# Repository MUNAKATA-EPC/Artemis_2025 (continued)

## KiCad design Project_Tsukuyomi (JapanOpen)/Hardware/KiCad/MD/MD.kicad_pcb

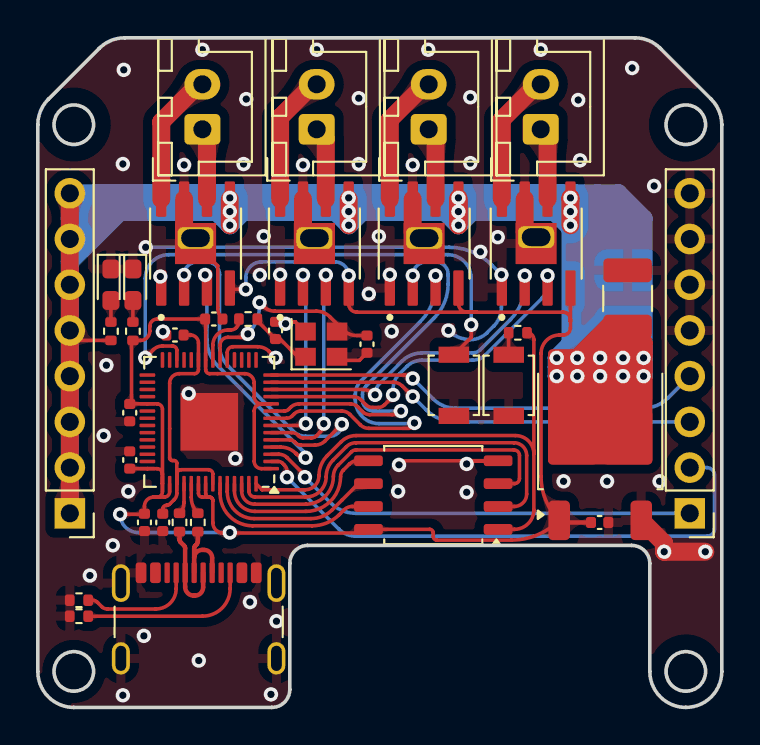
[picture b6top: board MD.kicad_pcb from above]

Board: 2 copper layers, 38.0 x 37.2 mm, 37 parts (0 on the bottom side), 43 nets.

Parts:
C1, C2: C_Small; C_0402_1005Metric
C3, C4, C5, C6, C7, C9, C11: 0.1μ; C_0402_1005Metric
C10: 0.1μ; C_1210_3225Metric_Pad1.33x2.70mm_HandSolder
D2, D3: LED; LED_0603_1608Metric_Pad1.05x0.95mm_HandSolder
J1: USB_C_Receptacle_USB2.0; USB_C_Receptacle_GCT_USB4105-xx-A_16P_TopMnt_Horizontal
J2, J3: Conn_01x08_Socket; PinHeader_1x08_P2.54mm_Vertical
J4, J5, J6, J7: Conn_01x02_Socket; JST_XH_B2B-XH-A_1x02_P2.50mm_Vertical
R1, R2: 5.1k; R_0402_1005Metric
R3, R4: 27; R_0402_1005Metric
R5, R6, R8: 1k; R_0402_1005Metric
R9: 100; R_0402_1005Metric
SW1, SW2: SW_Push; SW_SPST_B3U-1000P
U1: W25Q128JVS; SOIC-8_5.23x5.23mm_P1.27mm
U2: RP2040; QFN-56-1EP_7x7mm_P0.4mm_EP3.2x3.2mm
U3, U4, U5, U6: TB67H450FNG_EL; SOIC127P599X175-9N
U7: AZ1084-3.3; TO-252-2
Y1: Crystal_GND24; Crystal_SMD_2520-4Pin_2.5x2.0mm

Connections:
+1V1: C3.2, C4.2, U2.23 (DVDD), U2.45 (VREG_VOUT), U2.50 (DVDD)
+3.3V: C5.2, C6.2, C7.2, C9.2, C11.2, R9.1, U1.8 (VCC), U2.1 (IOVDD), U2.10 (IOVDD), U2.22 (IOVDD), U2.33 (IOVDD), U2.42 (IOVDD), U2.43 (ADC_AVDD), U2.44 (VREG_IN), U2.48 (USB_VDD), U2.49 (IOVDD), U3.4 (VREF), U4.4 (VREF), U5.4 (VREF), U6.4 (VREF), U7.2 (VO)
+12V: C10.2, J2.1, J2.2, J2.3, J2.4, J2.5, J2.6, J2.7, J2.8, R8.1, U3.5 (VM), U4.5 (VM), U5.5 (VM), U6.5 (VM), U7.3 (VO)
/BLDC1: J3.3, U2.13 (GPIO10)
/BLDC2: J3.4, U2.14 (GPIO11)
/BOOT: R5.1, SW2.1
/D+: R4.2, U2.47 (USB_DP)
/D-: R3.2, U2.46 (USB_DM)
/IN1A: U2.4 (GPIO2), U3.3 (IN1)
/IN1B: U2.5 (GPIO3), U3.2 (IN2)
/IN2A: U2.6 (GPIO4), U5.3 (IN1)
/IN2B: U2.7 (GPIO5), U5.2 (IN2)
/IN3A: U2.8 (GPIO6), U4.3 (IN1)
/IN3B: U2.9 (GPIO7), U4.2 (IN2)
/IN4A: U2.11 (GPIO8), U6.3 (IN1)
/IN4B: U2.12 (GPIO9), U6.2 (IN2)
/MDRX: J3.2, U2.2 (GPIO0)
/MDTX: J3.1, U2.3 (GPIO1)
/Motor1A: J4.1, U3.6 (OUT1)
/Motor1B: J4.2, U3.8 (OUT2)
/Motor2A: J5.1, U5.6 (OUT1)
/Motor2B: J5.2, U5.8 (OUT2)
/Motor3A: J6.1, U4.6 (OUT1)
/Motor3B: J6.2, U4.8 (OUT2)
/Motor4A: J7.1, U6.6 (OUT1)
/Motor4B: J7.2, U6.8 (OUT2)
/RUN: SW1.1, U2.26 (RUN)
GND: C1.2, C2.1, C3.1, C4.1, C5.1, C6.1, C7.1, C9.1, C10.1, C11.1, D2.1 (K), D3.1 (K), J1.A1 (GND), J1.A12 (GND), J1.B1 (GND), J1.B12 (GND), J1.S1 (SHIELD), J3.5, J3.6, J3.7, J3.8, R1.2, R2.2, SW1.2, SW2.2, U1.4 (GND), U2.19 (TESTEN), U2.57 (GND), U3.1 (GND), U3.7 (RS), U3.9 (GND), U4.1 (GND), U4.7 (RS), U4.9 (GND), U5.1 (GND), U5.7 (RS), U5.9 (GND), U6.1 (GND), U6.7 (RS), U6.9 (GND), U7.1 (GND), Y1.2, Y1.4
unnamed: C2.2, R6.2, Y1.1
unnamed: D2.2 (A), R8.2
unnamed: D3.2 (A), R9.2
unnamed: J1.A5 (CC1), R1.1
unnamed: J1.B5 (CC2), R2.1
unnamed: J1.A6 (D+), J1.B6 (D+), R4.1
unnamed: J1.A7 (D-), J1.B7 (D-), R3.1
unnamed: U1.6 (CLK), U2.52 (QSPI_SCLK)
unnamed: U1.5 (DI(IO0)), U2.53 (QSPI_SD0)
unnamed: U1.2 (DO(IO1)), U2.55 (QSPI_SD1)
unnamed: U1.3 (IO2), U2.54 (QSPI_SD2)
unnamed: U1.7 (IO3), U2.51 (QSPI_SD3)
unnamed: R5.2, U1.1 (~CS), U2.56 (QSPI_SS)
unnamed: C1.1, U2.20 (XIN), Y1.3
unnamed: R6.1, U2.21 (XOUT)

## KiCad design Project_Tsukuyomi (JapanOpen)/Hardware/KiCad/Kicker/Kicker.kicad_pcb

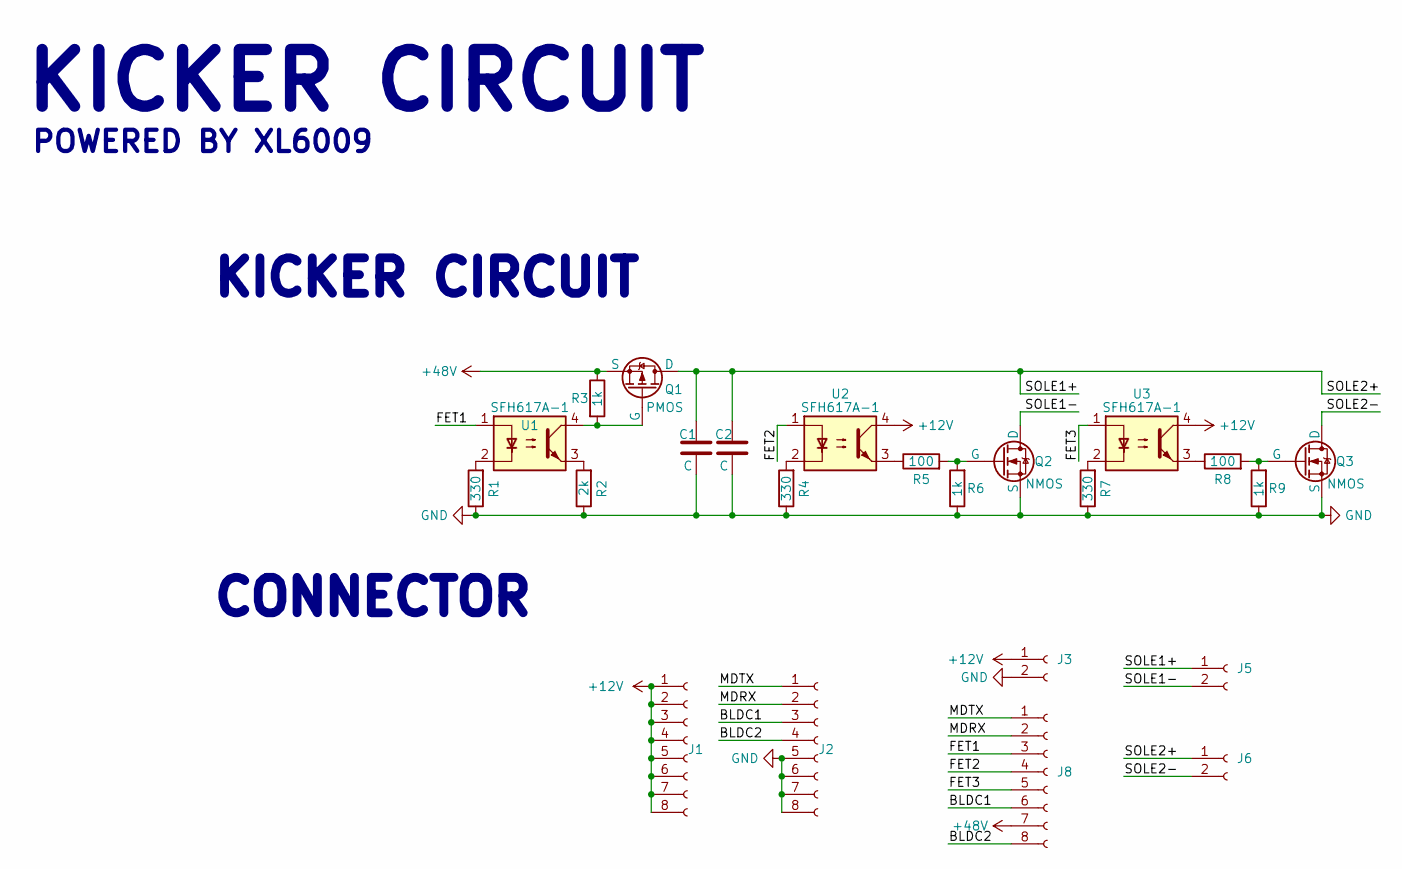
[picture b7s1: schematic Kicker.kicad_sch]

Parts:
C1, C2: C; JST_XH_B2B-XH-A_1x02_P2.50mm_Vertical
J1, J2: Conn_01x08_Socket; PinSocket_1x08_P2.54mm_Vertical
J3: Conn_01x02_Socket; AMASS_XT30PW-F_1x02_P2.50mm_Horizontal
J5, J6: Conn_01x02_Socket; JST_XH_B2B-XH-A_1x02_P2.50mm_Vertical
J8: Conn_01x08_Socket; PinHeader_2x06_P2.54mm_Horizontal
Q1: PMOS; TO-252-2
Q2, Q3: NMOS; LFPAK56
R1, R4, R7: 330; R_Axial_DIN0204_L3.6mm_D1.6mm_P5.08mm_Horizontal
R2: 2k; R_Axial_DIN0204_L3.6mm_D1.6mm_P5.08mm_Horizontal
R3, R6, R9: 1k; R_Axial_DIN0204_L3.6mm_D1.6mm_P5.08mm_Horizontal
R5, R8: 100; R_Axial_DIN0204_L3.6mm_D1.6mm_P5.08mm_Horizontal
U1, U2, U3: SFH617A-1; DIP-4_W7.62mm

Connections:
+12V: J1.1, J1.2, J1.3, J1.4, J1.5, J1.6, J1.7, J1.8, J3.1, U2.4, U3.4
+48V: Q1.3 (S), R3.1; also elsewhere on the board
/BLDC1: J2.3; also elsewhere on the board
/BLDC2: J2.4; also elsewhere on the board
/FET1: U1.1; also elsewhere on the board
/FET2: U2.1; also elsewhere on the board
/FET3: U3.1; also elsewhere on the board
/MDRX: J2.2; also elsewhere on the board
/MDTX: J2.1; also elsewhere on the board
/SOLE1+: C1.1, C2.1, J5.1, J6.1, Q1.1 (D)
/SOLE1-: J5.2, Q2.1 (D)
/SOLE2-: J6.2, Q3.1 (D)
GND: C1.2, C2.2, J2.5, J2.6, J2.7, J2.8, J3.2, Q2.3 (S), Q3.3 (S), R1.1, R2.1, R4.1, R6.1, R7.1, R9.1
unnamed: Q1.2 (G), R3.2, U1.4
unnamed: Q2.2 (G), R5.2, R6.2
unnamed: Q3.2 (G), R8.2, R9.2
unnamed: R1.2, U1.2
unnamed: R2.2, U1.3
unnamed: R4.2, U2.2
unnamed: R5.1, U2.3
unnamed: R7.2, U3.2
unnamed: R8.1, U3.3

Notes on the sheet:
KICKER CIRCUIT
POWERED BY XL6009
CONNECTOR

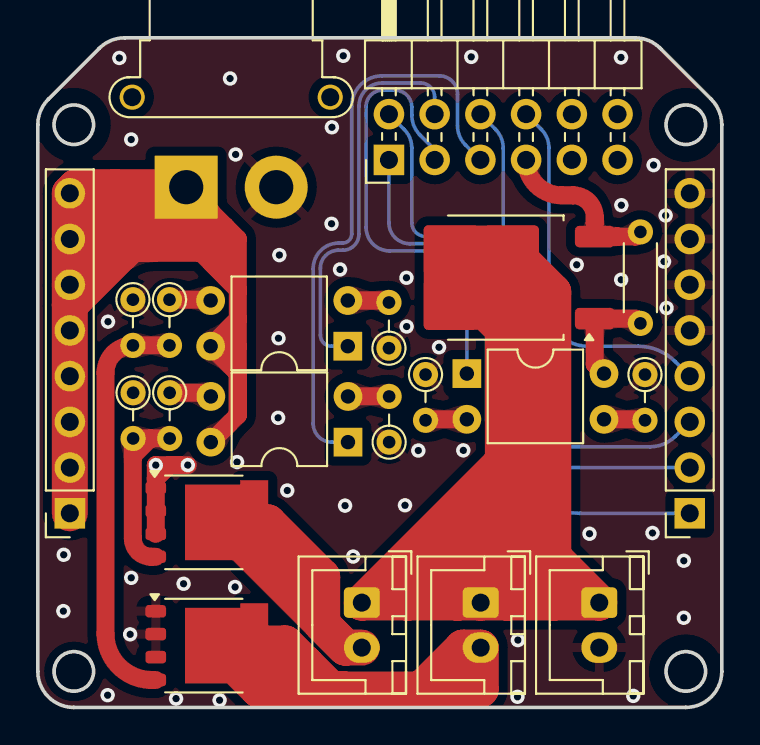
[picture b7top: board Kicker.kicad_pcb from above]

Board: 2 copper layers, 38.0 x 37.2 mm, 22 parts (0 on the bottom side), 22 nets.

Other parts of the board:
J4: Conn_01x08_Socket; PinHeader_2x06_P2.54mm_Horizontal

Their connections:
+48V: J4.7; also elsewhere on the board
/BLDC1: J4.6; also elsewhere on the board
/BLDC2: J4.8; also elsewhere on the board
/FET1: J4.3; also elsewhere on the board
/FET2: J4.4; also elsewhere on the board
/FET3: J4.5; also elsewhere on the board
/MDRX: J4.2; also elsewhere on the board
/MDTX: J4.1; also elsewhere on the board

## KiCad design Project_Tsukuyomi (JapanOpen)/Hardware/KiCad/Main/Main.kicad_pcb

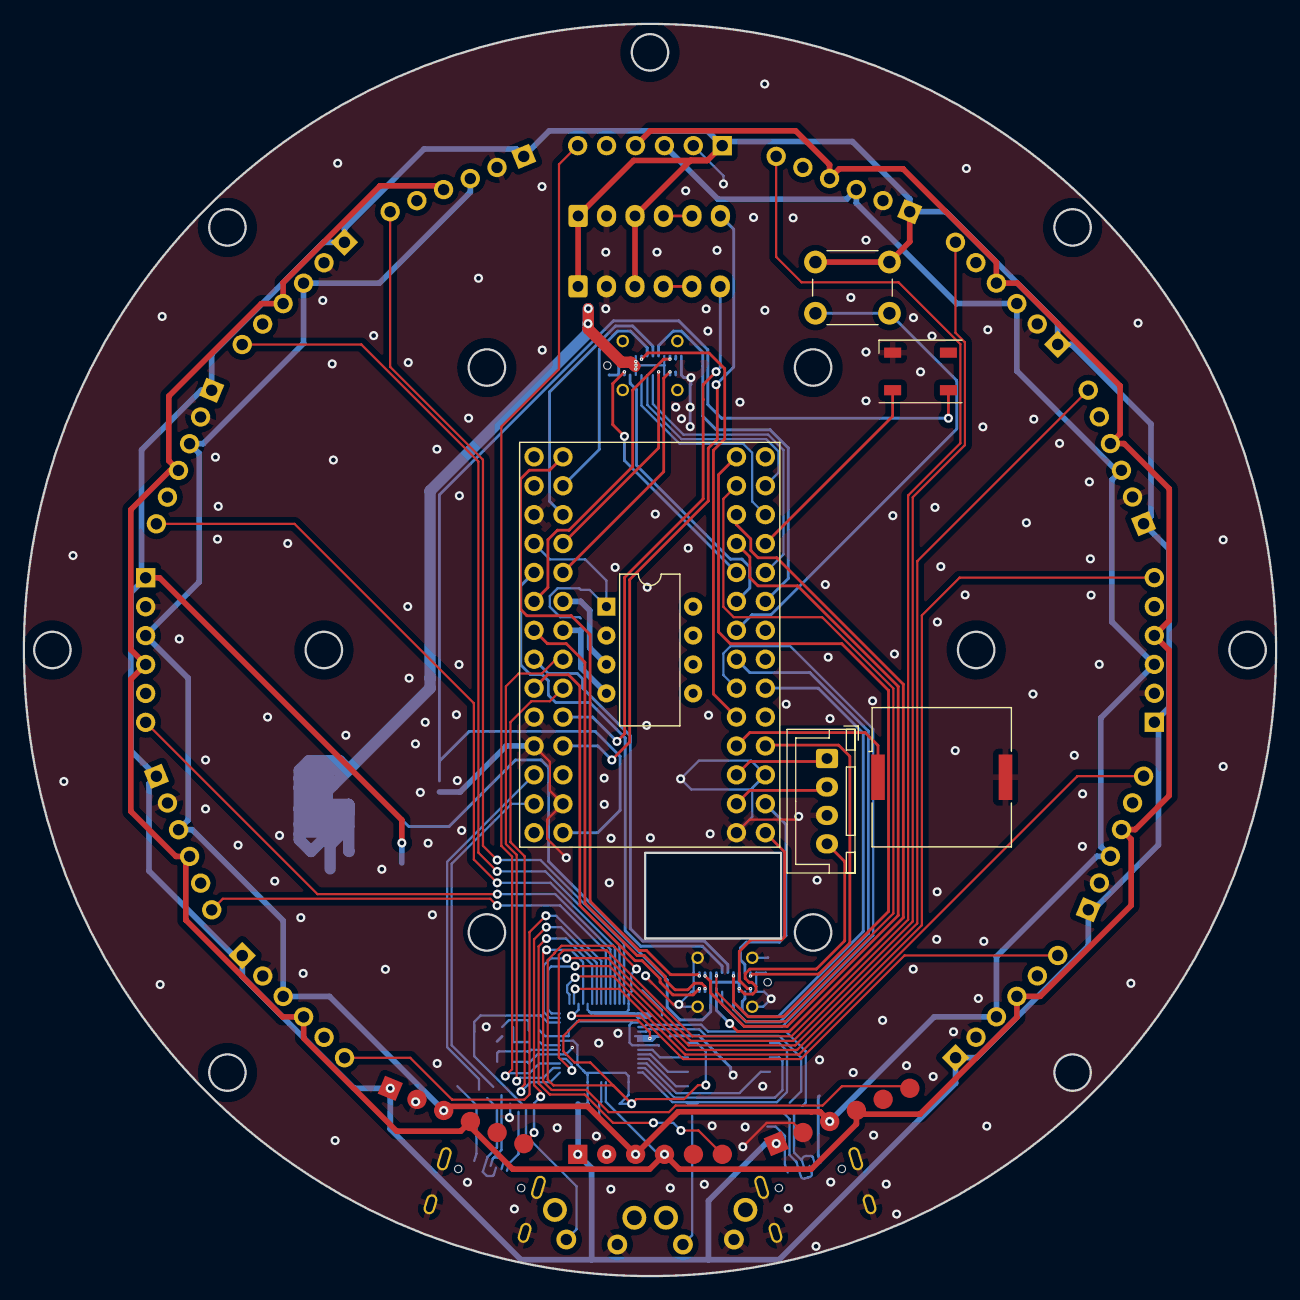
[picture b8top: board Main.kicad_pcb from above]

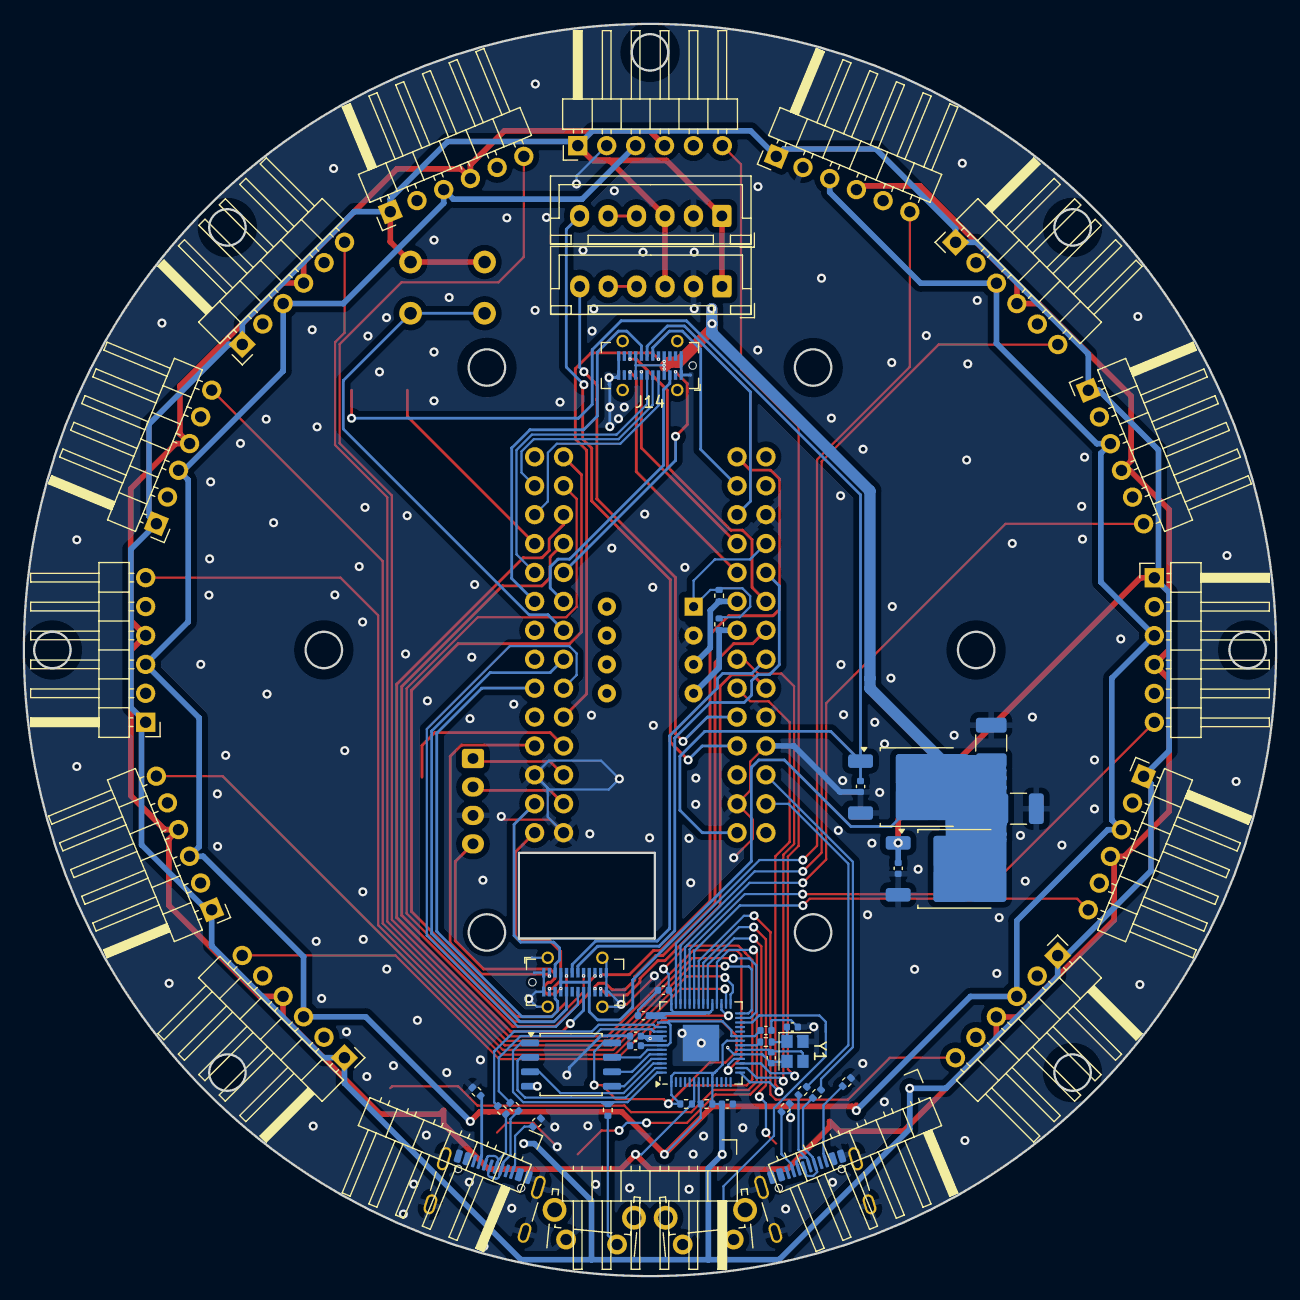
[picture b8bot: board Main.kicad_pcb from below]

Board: 2 copper layers, 110.0 x 110.0 mm, 61 parts (55 on the bottom side), 86 nets.

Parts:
BZ1: Buzzer; Buzzer_Murata_PKLCS1212E
C1, C2: C_Small; C_0402_1005Metric
C3, C4: C; C_1210_3225Metric_Pad1.33x2.70mm_HandSolder
C5, C6, C7, C8, C9, C10, C11, C12: C; C_0402_1005Metric
D1: WS2812B; LED_WS2812B_PLCC4_5.0x5.0mm_P3.2mm
J1, J20: USB_C_Receptacle_USB2.0; USB_C_Receptacle_GCT_USB4105-xx-A_16P_TopMnt_Horizontal
J2, J3, J4, J5, J6, J7, J8, J9, J10, J11, J12, J13, J15, J16, J17, J18: Conn_01x06_Socket; PinHeader_1x06_P2.54mm_Horizontal
J14, J19: UJ32-C-V-G-TH-5-P24-TR; USB_C_Receptacle_GCT_USB4115-03-C
J21: Conn_01x04_Socket; JST_XH_B4B-XH-A_1x04_P2.50mm_Vertical
J22, J23: Conn_01x06_Socket; JST_XH_B6B-XH-A_1x06_P2.50mm_Vertical
R1, R2: 1k; R_0402_1005Metric
R3, R4, R7, R8, R9, R10, R13, R14: 5.1k; R_0402_1005Metric
R5, R6, R11, R12: 27; R_0402_1005Metric
SW1, SW2: SW_Push; SW_Tactile_SPST_Angled_PTS645Vx31-2LFS
SW3: SW_Push; SW_PUSH_6mm
U1: W25Q128JVS; SOIC-8_5.23x5.23mm_P1.27mm
U2: RP2040; QFN-56-1EP_7x7mm_P0.4mm_EP3.2x3.2mm
U3: AZ1084-5.0; TO-252-2
U4: AZ1084-3.3; TO-252-2
U5: Teensy4.0; Teensy_Brakeout
U6: AE-BNO055-BO; CERDIP-8_W7.62mm_SideBrazed
Y1: Crystal_GND24; Crystal_SMD_2520-4Pin_2.5x2.0mm

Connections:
+1V1: C7.1, C8.1, U2.23 (DVDD), U2.45 (VREG_VOUT), U2.50 (DVDD)
+3.3V: C6.1, C9.1, C10.1, C11.1, C12.1, J2.1, J3.1, J4.1, J5.1, J6.1, J7.1, J8.1, J9.1, J10.1, J11.1, J12.1, J13.1, J15.1, J16.1, J17.1, J18.1, J22.1, J22.3, J23.1, J23.3, R7.2, R8.2, R13.2, R14.2, SW3.2, U1.8 (VCC), U2.1 (IOVDD), U2.10 (IOVDD), U2.22 (IOVDD), U2.33 (IOVDD), U2.42 (IOVDD), U2.43 (ADC_AVDD), U2.44 (VREG_IN), U2.48 (USB_VDD), U2.49 (IOVDD), U4.2 (VO), U5.31 (3V3), U6.0 (VIN)
+5V: C5.1, D1.1 (VDD), U3.2 (VO), U5.33 (VIN)
+12V: C3.1, C4.1, J14.A4 (VBUS), J14.A9 (VBUS), J14.B4 (VBUS), J14.B9 (VBUS), J19.A4 (VBUS), J19.A9 (VBUS), J19.B4 (VBUS), J19.B9 (VBUS), J21.4, U3.3 (VI), U4.3 (VI)
/1: J2.6, U2.17 (GPIO14)
/2: J6.6, U2.18 (GPIO15)
/3: J10.6, U2.27 (GPIO16)
/4: J15.6, U2.28 (GPIO17)
/5: J3.6, U2.29 (GPIO18)
/6: J7.6, U2.30 (GPIO19)
/7: J11.6, U2.31 (GPIO20)
/8: J16.6, U2.32 (GPIO21)
/9: J4.6, U2.34 (GPIO22)
/10: J8.6, U2.35 (GPIO23)
/11: J12.6, U2.36 (GPIO24)
/12: J17.6, U2.37 (GPIO25)
/13: J5.6, U2.38 (GPIO26_ADC0)
/14: J9.6, U2.39 (GPIO27_ADC1)
/15: J13.6, U2.40 (GPIO28_ADC2)
/16: J18.6, U2.41 (GPIO29_ADC3)
/BOOT: R1.1, SW2.1
/CAMRX: J21.2, U5.2 (0_RX1_CRX2_CS1)
/CAMTX: J21.1, U5.3 (1_TX1_CTX2_MISO1)
/CS: J19.B5 (CC2), U5.12 (10_CS_MQSR)
/D+: R6.2, U2.47 (USB_DP)
/D-: R5.2, U2.46 (USB_DM)
/DC: J19.B2 (SSTXP2), U5.38 (27_A13_SCK1)
/FET1: J14.A6 (DP1), U5.41 (30_CRX3)
/FET2: J14.A7 (DN1), U5.42 (31_CTX3)
/FET3: J14.A5 (CC1), U5.43 (32_OUT1B)
/LineRX: J14.B6 (DP2), U5.22 (15_A1_RX3_SPDIF_IN)
/LineTX: J14.B7 (DN2), U5.21 (14_A0_TX3_SPDIF_OUT)
/Line_NeoPixel: J14.B8 (SBU2), U5.5 (3_LRCLK2)
/MDRX: J14.A3 (SSTXN1), U5.9 (7_RX2_OUT1A)
/MDTX: J14.A2 (SSTXP1), U5.10 (8_TX2_IN1)
/MISO: J19.A5 (CC1), U5.14 (12_MISO_MQSL)
/MOSI: J19.A8 (SBU1), U5.13 (11_MOSI_CTX1)
/Main_SCL: R14.1, U5.26 (19_A5_SCL0), U6.3 (SCL)
/Main_SDA: R13.1, U5.25 (18_A4_SDA0), U6.2 (SDA)
/MouseRX: J14.B3 (SSTXN2), U5.39 (28_RX7)
/MouseTX: J14.B5 (CC2), U5.40 (29_TX7)
/NeoPixel: J19.B6 (DP2), U5.6 (4_BCLK2)
/RESET: J19.B3 (SSTXN2), U5.37 (26_A12_MOSI1)
/RUN: SW1.1, U2.26 (RUN)
/SCK: J19.A11 (SSRXP2), U5.20 (13_SCK_CRX1_LED)
/SCL: J2.3, J3.3, J4.3, J5.3, J6.3, J7.3, J8.3, J9.3, J10.3, J11.3, J12.3, J13.3, J15.3, J16.3, J17.3, J18.3, R7.1, U2.7 (GPIO5)
/SDA: J2.4, J3.4, J4.4, J5.4, J6.4, J7.4, J8.4, J9.4, J10.4, J11.4, J12.4, J13.4, J15.4, J16.4, J17.4, J18.4, R8.1, U2.6 (GPIO4)
/SD＿CS: J19.A2 (SSTXP1), U5.48 (36_CLK_CS2)
/SD＿MISO: J19.B11 (SSRXP1), U5.45 (34_DAT1_MISO2)
/SD＿MOSI: J19.A3 (SSTXN1), U5.46 (35_DAT0_MOSI2)
/SD＿SCK: J19.B10 (SSRXN1), U5.50 (37_CMD_SCK2)
/START: J19.B8 (SBU2), U5.7 (5_IN2)
/SUB: SW3.1, U5.8 (6_OUT1D)
/SUB_Ind: D1.4 (DIN), U5.44 (33_MCLK2)
/TD+: R12.2, U5.54 (D+)
/TD-: R11.2, U5.53 (D-)
/T_CS: J19.A10 (SSRXN2), U5.11 (9_OUT1C)
/ToF_RX: U2.15 (GPIO12), U5.28 (21_A7_RX5_BCLK1)
/ToF_TX: U2.16 (GPIO13), U5.27 (20_A6_TX5_LRCLK1)
/Touch_B: J23.6, U5.30 (23_A9_CRX1_MCLK1)
/Touch_F: J22.6, U5.29 (22_A8_CTX1)
/TweRX: J19.A6 (DP1), U5.36 (25_A11_RX6_SDA2)
/TweTX: J19.A7 (DN1), U5.35 (24_A10_TX6_SCL2)
/UART_RX: J14.A8 (SBU1), U5.23 (16_A2_RX4_SCL1)
/UART_TX: J14.A10 (SSRXN2), U5.24 (17_A3_TX4_SDA1)
GND: BZ1.2 (+), C1.2, C2.1, C3.2, C4.2, C5.2, C6.2, C7.2, C8.2, C9.2, C10.2, C11.2, C12.2, D1.3 (VSS), J1.A1 (GND), J1.A12 (GND), J1.B1 (GND), J1.B12 (GND), J1.S1 (SHIELD), J2.2, J3.2, J4.2, J5.2, J6.2, J7.2, J8.2, J9.2, J10.2, J11.2, J12.2, J13.2, J14.A1 (GND), J14.A12 (GND), J14.B1 (GND), J14.B12 (GND), J15.2, J16.2, J17.2, J18.2, J19.A1 (GND), J19.A12 (GND), J19.B1 (GND), J19.B12 (GND), J19.S1, J20.A1 (GND), J20.A12 (GND), J20.B1 (GND), J20.B12 (GND), J20.S1 (SHIELD), J21.3, J22.2, J23.2, R3.2, R4.2, R9.2, R10.2, SW1.2, SW2.2, U1.4 (GND), U2.19 (TESTEN), U2.57 (GND), U3.1 (GND), U4.1 (GND), U5.1 (GND), U6.1 (GND), Y1.2, Y1.4
unnamed: BZ1.1 (-), U5.4 (2_OUT2)
unnamed: C2.2, R2.2, Y1.1
unnamed: J1.A5 (CC1), R3.1
unnamed: J1.B5 (CC2), R4.1
unnamed: J1.A6 (D+), J1.B6 (D+), R6.1
unnamed: J1.A7 (D-), J1.B7 (D-), R5.1
unnamed: J20.A5 (CC1), R9.1
unnamed: J20.B5 (CC2), R10.1
unnamed: J20.A6 (D+), J20.B6 (D+), R12.1
unnamed: J20.A7 (D-), J20.B7 (D-), R11.1
unnamed: J22.4, J22.5
unnamed: J23.4, J23.5
unnamed: U1.6 (CLK), U2.52 (QSPI_SCLK)
unnamed: U1.5 (DI(IO0)), U2.53 (QSPI_SD0)
unnamed: U1.2 (DO(IO1)), U2.55 (QSPI_SD1)
unnamed: U1.3 (IO2), U2.54 (QSPI_SD2)
unnamed: U1.7 (IO3), U2.51 (QSPI_SD3)
unnamed: R1.2, U1.1 (~CS), U2.56 (QSPI_SS)
unnamed: C1.1, U2.20 (XIN), Y1.3
unnamed: R2.1, U2.21 (XOUT)

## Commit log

2024-06-09 なんか色々
2024-10-16 プログラム準備
2024-11-08 初めてのunitV
2024-12-01 カメラのデータ取得・エンジェルラインのデータ取得・UI仮作成中
2024-12-02 プログラム整備、プレゼンシート作成①
2024-12-02 ちょい微調整
2024-12-03 プレゼンシート
2024-12-03 アタッカープログラム構想作成、UI部分仮組み立て、センサー変数の定義
2024-12-03 フォルダ階層の変更
2024-12-04 chan
2024-12-04 プレゼンシート仮完成
2024-12-04 mata bityousei
2024-12-06 ボール見えた・ライン見えた・ゴール見えた
2024-12-06 カメラv2
2024-12-07 Lets go Fukuoka Node
2024-12-10 hue~
2024-12-22 Tsukuyomiは全国大会用プログラム
2024-12-24 キーパー原型
2024-12-27 とりあえず資料用フォルダ追加
2025-01-07 unko
2025-01-08 現状復帰
2025-01-09 ボールと手の区別
2025-01-11 めちゃくちゃよさげ
2025-01-11 ボールと手が同じときは赤を下げる
2025-01-11 lets goooo
2025-01-11 voeeeeeeeeeeee
2025-01-11 KiCadデータ追加
    頑張ってます💪
2025-01-13 Digikey
2025-01-29 ファームウェア
2025-01-29 全国用に後で移す
2025-01-30 ファイル整理
2025-01-30 メインプログラム更新
2025-02-10 カメラのプログラム
2025-02-11 プレゼンシート下地
2025-02-14 カメラプログラム
2025-02-15 プレゼンシート更新
2025-02-15 昇圧までは動いた
2025-02-17 カメラ360度
2025-02-17 電圧取れた
2025-02-18 プレゼンシート8割完成！
2025-02-18 微調整②
2025-02-18 あと画像の貼り付けと研究のみ！
2025-02-18 やっぱもうちょっと微調整
2025-02-19 プレゼン更新
2025-02-19 プレゼン修正
2025-02-19 プレゼンシート調整
2025-02-20 NeoPixelテスト
2025-02-20 プレゼンシート9割完成
2025-02-23 KiCad変更
    ごめんさい。溜めました
2025-02-23 カメラ 前後交代
2025-02-23 PIDまで行った
2025-02-24 thinking
2025-02-26 ボール追いました
2025-02-28 SE><
2025-02-28 次回 カメラ：上を外して確認
2025-03-08 カメラとモタドラとTeensyと
2025-03-13 回り込み
2025-03-14 回り込み修正
2025-03-16 fucking ball chasing
2025-03-16 回り込みj修正
2025-03-16 hello cpp world
2025-03-16 シリアル反応なし.
2025-03-17 fucking computer
2025-03-17 UIとかラインとか処理追加
2025-03-17 エンジェルラインの角度処理追加
2025-03-18 line is very goooooooooooood
2025-03-20 HAPPY TRIGGER
2025-03-20 LETS GOOOOOOOOOOOOO
2025-03-20 キーパー実装①
2025-03-21 ;thinking keeper;
2025-03-21 Revert ";thinking keeper;"
    This reverts commit d8e245b7f309ed206e60094b9ad9a8fcfb07b2bc.
2025-03-21 Reapply ";thinking keeper;"
    This reverts commit 7145ae71b8c6e74d14a363132d6ce91db272cc4e.
2025-03-21 ソフトじゃどうにもならんかも.
2025-03-22 fucking seeduino
2025-03-22 キーパー調整②
2025-03-25 not saying.
2025-03-26 悪足掻き
2025-03-27 ディフェンダーで速度制御を使うかどうかを設定できるように
2025-03-31 溜まった変更大放出
